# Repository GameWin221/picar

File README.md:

# picar
Car with autonomous and remote-controlled capabilities controlled by Raspberry Pi 5 and a CH32V003 microcontroller. Features a custom made mainboard PCB responsible for controlling motors, servos and delivering power to the RPi 5.

It is capable of real-time remote control with a gamepad (e.g. XBox One gamepad) alongside a live WebRTC stream from its camera.
Moreover, simple autonomous driving is possible by following an RGB tracking marker.

### Version 3 Early (still the old frame from V2)

*PiCar with the tracking marker next to it*

## Future ideas 
- Add a ToF sensor and use it in tandem with the DepthAnything V2 depth estimation model to acquire real (approximated) depth information from the camera.

# Hardware
- Battery pack composed of 3x 18650 cells connected in series. It has both XT60 connector for the main power and 4-pin JST-XH used for balancing.
- SG92R micro servo used for steering
- Raspberry Pi 5 8GB
- Raspberry Pi Camera HD v2 8MPx
- Custom PCB mainboard responsible for controlling motors, servos and delivering power to the RPi 5. (More on that [below](#pcb-mainboard))
- Custom 3D-printed frame and steering system (files available in the "designs" directory)
- 4x 60x8mm black Pololu 1420 wheels
- 2x 6x13x5mm bearings for the front wheels
- 2x N20-BT07 micro 100:1 320RPM 12V motors
- M3 screws used for assembling the frame and wheels together

## PCB mainboard

*/pcb_main_board/pcb_main_board_schematic.svg*

*/images/pcb_main_board1.png*

### On-board microcontroller

CH32V003 MCU is the main controller of the whole board. It is responsible for controlling the motor drivers, servo motors and monitoring the battery voltage. It communicates with the Raspberry Pi 5 over I2C.

### Battery to RPi 5 voltage step-down

The battery input voltage is first filtered by the input low-ESR capacitor and capped to 15V by a SMBJ15A TVS diode. Then the MP2338 IC is used to reliably step-down the battery voltage from 9V-12.6V range to ~5.1V that is then connected via a USB-C cable to the RPi 5. The MP2338's GND pin is connected to wide copper traces with vias in order to improve cooling.

### Motor control

TB6612FNG IC is used to drive both of the main motors. The IC logic is driven by PWM signals generated by the on-board microcontroller. The PWM frequency can be adjusted from the software layer if the user wants to prioritize peak power or to minimize the audible switching noise. The lower the frequency, the more efficient the motors are, but the louder they become.

### Servo control

The mainboard is capable of running 4 separate hardware PWM signals at once which are generated by the on-board microcontroller. The servo motors are powered with 4.8V generated by another MP2238 IC configured in the same way as the other one used for powering RPi 5, except for the output voltage. The servo section also has a 3-pin header for each signal channel in order to simplify the connections. There are more servo channels than are currently needed for future-proofing reasons. *e.g. allowing the camera to have adjustable yaw and pitch in the future.*

### Wheels

The front wheels are fastened to their mounts with short M3 screws. Those mounts then clip into the ball bearings, working similarly to LEGO Technic connections. A pin with the correct diameter and side cuts is pushed into the bearing hole and holds firmly enough for normal operation. The rear wheels are press-fitted onto the motor shafts:

Front wheel assembly disassembled in Fusion 360:

# Software and control

## Frontend
**PiCar** can be controlled through a simple Websockets-based web interface (`/car/software/index.html`). When you run the Python `"Remote Control" main loop` an HTTP server starts up and reveals the visual interface at `http://{raspberry_pi_5_ip}:8000`. There are two sliders that control it but the better (and way cooler) option is to **use a gamepad and control the car this way**. The website automatically detects connected gamepads and lets the user steer by using both triggers for accelerating and braking and the left thumbstick for steering. It is also possible to set the motors PWM switching frequency.

There also is a viewport for watching the live feed coming from the camera connected to the RPi 5. The stream source must be a WebRTC source which can be created easily by using [MediaMTX](https://github.com/bluenviron/mediamtx). You can find the working `mediamtx.yml` file I use to enable the stream at `/car/mediamtx.yml`. Once mediamtx starts with my provided config, the camera can be accessed by connecting via WebRTC to `{raspberry_pi_5_ip}:8889/rpi`.

## Vision

Autonomous driving, for now, is a simple computer vision algorithm that searches for a special marker with three key colors: red, green, and blue on the live feed streamed from the Raspberry Pi Camera HD v2 8MPx.

The camera feed is first filtered bilaterally to remove small details and noise in the subsequent marker search. Then gamma is adjusted to increase contrast, and the resulting image is binarized so that the SimpleBlobDetector from the OpenCV library can detect three circles. Finally, the algorithm checks whether the circles are "inside" the potentially found marker—i.e., whether they are not shifted from the averaged center by more than one standard deviation. If they are not, we can be certain that the marker has been found.

Below is a visualization of how the marker is seen by the algorithm:

When the marker is found, the vehicle drives forward and turns so that the center of the marker aligns with the center of the camera's view. This is sufficient to effectively track the marker.

### Future Vision Enhancement

I plan to use a ToF distance sensor in tandem with the computer vision model **DepthAnythingV2**, which estimates depth using a single camera. This combination will allow me to acquire approximate (yet sufficiently accurate) distance information of everything visible in the front camera. This data will enable shape detection by contours and autonomous obstacle avoidance.

## Firmware

The CH32V003 microcontroller runs a firmware that acts as a PWM and motor control interface for the Raspberry Pi 5. The firmware exposes a register-based interface over I2C using slave address `0x17`, allowing the RPi to elegantly control all aspects of motor and servo operation.

### I2C Communication Protocol

The firmware operates as an I2C slave that receives write-only commands structured as `[register_id, data_low, data_high]`. Each register controls a specific aspect of the system:

| Register | Purpose                           | Range            |
|----------|-----------------------------------|------------------|
| 1        | TIM1 (servo) frequency            | 1 - 48000 Hz     |
| 2        | TIM2 (motor) frequency            | 1 - 48000 Hz     |
| 4-7      | Servo CH1-CH4 duty cycle          | 0 - PWM_PERIOD(1000)         |
| 10-11    | Motor PWM (right/left) duty cycle | 0 - PWM_PERIOD(1000)         |
| 12       | Motor direction control           | Bit 0: DIRF, Bit 8: DIRB |

## Building the code

### RPi 5 Python
Configure the virtual environment if you need and run `pip install -r requirements.txt` while being in the `/car/software` directory to download the necessary packages. Downlaod opencv as a standalone package. Once everything is downloaded, run `python main.py` and it should work fine.

#### Enabling the necessary RPi 5 options
To make I2C communication work properly, enable it either with the `raspi-config` command or by manually adding the necessary lines to the `/boot/firmware/config.txt` file:

```
dtparam=i2c_arm=on
dtparam=i2c_arm_baudrate=80000 # or any other as you wish
dtparam=i2s=on
```

Also enable the camera detection in the same way. Here is the line for `/boot/firmware/config.txt`:

```
camera_auto_detect=1
```

### CH32V003 C Firmware
Downloading and building it through MounRiver Studio IDE is the easiest route to go. This repo already has project files that work out of the box when you open them with the IDE. Just press F7 and it should build perfectly fine.

#### Flashing it
You'll need a **WCH LinkE** programmer in order to flash the firmware to the chip. Once you have it, connect GND to GND and the SWDIO pin to the chip's SWIO pin according to its datasheet *(It's pin PD1 for CH32V003A4M6)*. The chip must be powered either from the programmer's voltage pin or externally during flashing.

Now go to MounRiver Studio IDE and press F7 to build your project and then F8 to flash it having the WCH LinkE programmer plugged into your computer at the same time, **note that flashing your code does not rebuild it automatically, you have to remember to press F7 each time.**. You can also change the flashing configuration but it's almost always good to go by default. *(called Download Configuration)*:

Do not press or hold the reset button during flashing (the NRST pin)

# Archive

Take a look at the [PROGRESS.md markdown file](/PROGRESS.md) to see how the project evolved over time.

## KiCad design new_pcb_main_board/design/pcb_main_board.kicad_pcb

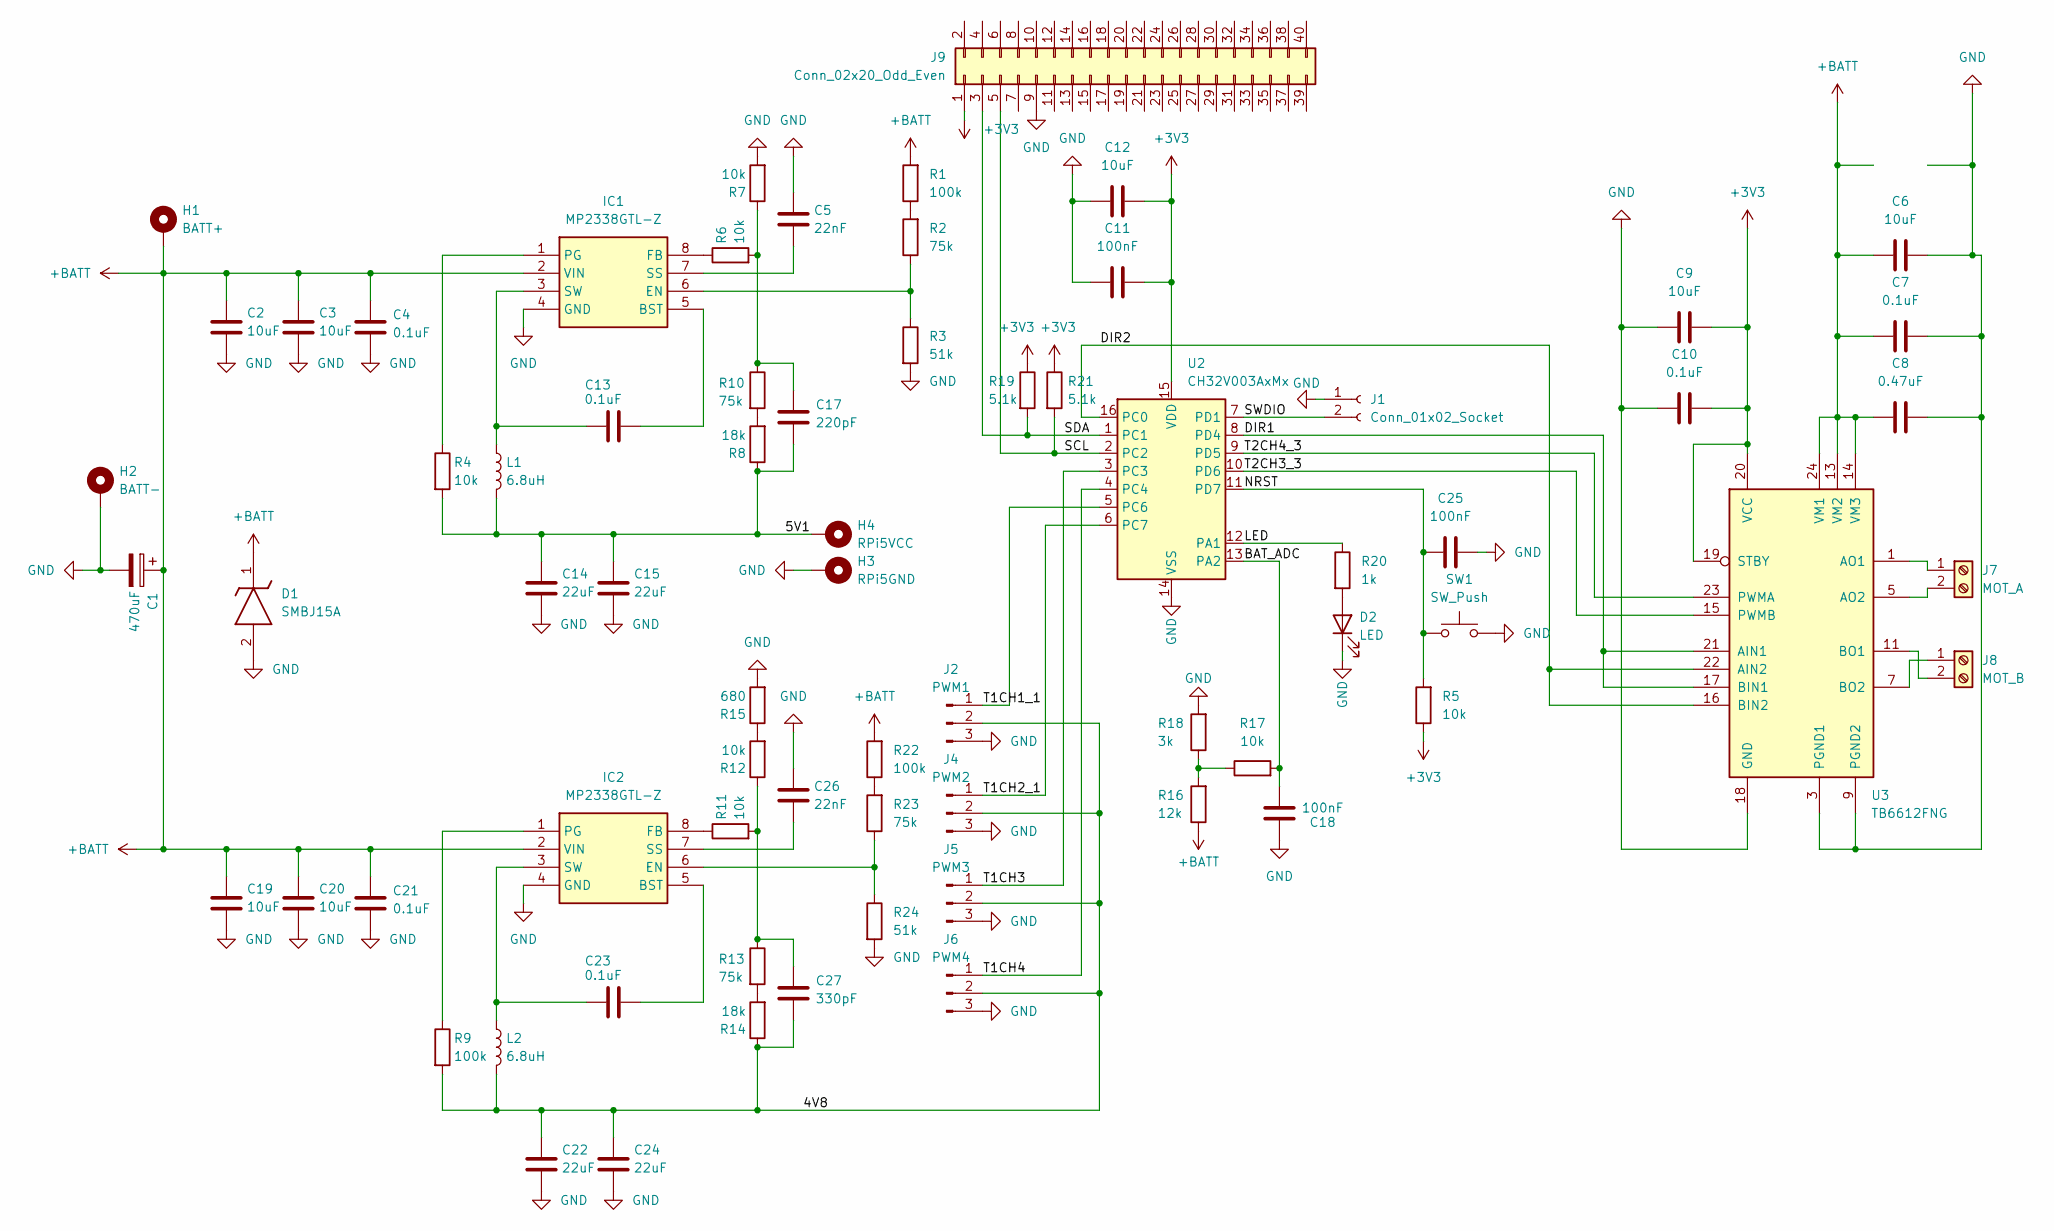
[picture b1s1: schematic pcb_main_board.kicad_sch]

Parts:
C1: 470uF; CP_Radial_D8.0mm_P3.50mm
C2, C3, C6, C9, C12, C19, C20: 10uF; C_0805_2012Metric
C4, C7, C10, C13, C21, C23: 0.1uF; C_0805_2012Metric
C5, C26: 22nF; C_0805_2012Metric
C8: 0.47uF; C_0805_2012Metric
C11, C18, C25: 100nF; C_0805_2012Metric
C14, C15, C22, C24: 22uF; C_0805_2012Metric_Pad1.18x1.45mm_HandSolder
C17: 220pF; C_0805_2012Metric
C27: 330pF; C_0805_2012Metric
D1: SMBJ15A; DIOM5436X244N; Mouser Part Number 78-SMBJ15A
D2: LED; LED_0805_2012Metric_Pad1.15x1.40mm_HandSolder
H1: BATT+; SolderWire-1sqmm_1x01_D1.4mm_OD3.9mm
H2: BATT-; SolderWire-1sqmm_1x01_D1.4mm_OD3.9mm
H3: RPi5GND; SolderWire-0.5sqmm_1x01_D0.9mm_OD2.3mm
H4: RPi5VCC; SolderWire-0.5sqmm_1x01_D0.9mm_OD2.3mm
IC1, IC2: MP2338GTL-Z; SOT-583-8; Mouser Part Number 946-MP2338GTL-Z
J1: Conn_01x02_Socket; PinSocket_1x02_P2.54mm_Vertical
J2: PWM1; PinHeader_1x03_P2.54mm_Vertical
J4: PWM2; PinHeader_1x03_P2.54mm_Vertical
J5: PWM3; PinHeader_1x03_P2.54mm_Vertical
J6: PWM4; PinHeader_1x03_P2.54mm_Vertical
J7: MOT_A; TerminalBlock_MaiXu_MX126-5.0-02P_1x02_P5.00mm
J8: MOT_B; TerminalBlock_MaiXu_MX126-5.0-02P_1x02_P5.00mm
J9: Conn_02x20_Odd_Even; PinSocket_2x20_P2.54mm_Vertical
L1, L2: 6.8uH; L_Chilisin_BMRF00101040
R1, R9, R22: 100k; R_0805_2012Metric
R2, R10, R13, R23: 75k; R_0805_2012Metric
R3, R24: 51k; R_0805_2012Metric
R4, R5, R6, R7, R11, R12, R17: 10k; R_0805_2012Metric
R8, R14: 18k; R_0805_2012Metric
R15: 680; R_0805_2012Metric
R16: 12k; R_0805_2012Metric
R18: 3k; R_0805_2012Metric
R19, R21: 5.1k; R_0805_2012Metric
R20: 1k; R_0805_2012Metric
SW1: SW_Push; SW_PUSH_6mm
U2: CH32V003AxMx; STC_SOP-16_3.9x9.9mm_P1.27mm
U3: TB6612FNG; SSOP-24_5.3x8.2mm_P0.65mm

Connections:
+3V3: C9.2, C10.2, C11.2, C12.2, J9.1, R5.1, R19.1, R21.1, U2.15 (VDD), U3.19 (STBY), U3.20 (VCC)
+BATT: C1.1, C2.1, C3.1, C4.1, C6.1, C7.1, C8.1, C19.1, C20.1, C21.1, D1.1 (K), H1.1, IC1.2 (VIN), IC2.2 (VIN), R1.2, R16.1, R22.2, U3.13 (VM2), U3.14 (VM3), U3.24 (VM1)
/4V8: C22.1, C24.1, C27.2, J2.2, J4.2, J5.2, J6.2, L2.2, R9.2, R14.1
/5V1: C14.1, C15.1, C17.2, H4.1, L1.2, R4.2, R8.1
/BAT_ADC: C18.2, R17.2, U2.13 (PA2)
/DIR1: U2.8 (PD4), U3.17 (BIN1), U3.21 (AIN1)
/DIR2: U2.16 (PC0), U3.16 (BIN2), U3.22 (AIN2)
/LED: R20.1, U2.12 (PA1)
/NRST: C25.1, R5.2, SW1.1, U2.11 (PD7)
/SCL: J9.5, R21.2, U2.2 (PC2)
/SDA: J9.3, R19.2, U2.1 (PC1)
/SWDIO: J1.2, U2.7 (PD1)
/T1CH1_1: J2.1, U2.5 (PC6)
/T1CH2_1: J4.1, U2.6 (PC7)
/T1CH3: J5.1, U2.3 (PC3)
/T1CH4: J6.1, U2.4 (PC4)
/T2CH3_3: U2.10 (PD6), U3.15 (PWMB)
/T2CH4_3: U2.9 (PD5), U3.23 (PWMA)
GND: C1.2, C2.2, C3.2, C4.2, C5.1, C6.2, C7.2, C8.2, C9.1, C10.1, C11.1, C12.1, C14.2, C15.2, C18.1, C19.2, C20.2, C21.2, C22.2, C24.2, C25.2, C26.1, D1.2 (A), D2.1 (K), H2.1, H3.1, IC1.4 (GND), IC2.4 (GND), J1.1, J2.3, J4.3, J5.3, J6.3, J9.9, R3.2, R7.2, R15.2, R18.2, R24.2, SW1.2, U2.14 (VSS), U3.3 (PGND1), U3.4 (PGND1), U3.9 (PGND2), U3.10 (PGND2), U3.18 (GND)
unnamed: C17.1, R6.2, R7.1, R10.1
unnamed: C27.1, R11.2, R12.1, R13.1
unnamed: D2.2 (A), R20.2
unnamed: C13.2, IC1.5 (BST)
unnamed: IC1.6 (EN), R2.1, R3.1
unnamed: IC1.8 (FB), R6.1
unnamed: IC1.1 (PG), R4.1
unnamed: C5.2, IC1.7 (SS)
unnamed: C13.1, IC1.3 (SW), L1.1
unnamed: C23.2, IC2.5 (BST)
unnamed: IC2.6 (EN), R23.1, R24.1
unnamed: IC2.8 (FB), R11.1
unnamed: IC2.1 (PG), R9.1
unnamed: C26.2, IC2.7 (SS)
unnamed: C23.1, IC2.3 (SW), L2.1
unnamed: J7.1, U3.1 (AO1), U3.2 (AO1)
unnamed: J7.2, U3.5 (AO2), U3.6 (AO2)
unnamed: J8.1, U3.7 (BO2), U3.8 (BO2)
unnamed: J8.2, U3.11 (BO1), U3.12 (BO1)
unnamed: R1.1, R2.2
unnamed: R8.2, R10.2
unnamed: R12.2, R15.1
unnamed: R13.2, R14.2
unnamed: R16.2, R17.1, R18.1
unnamed: R22.1, R23.2

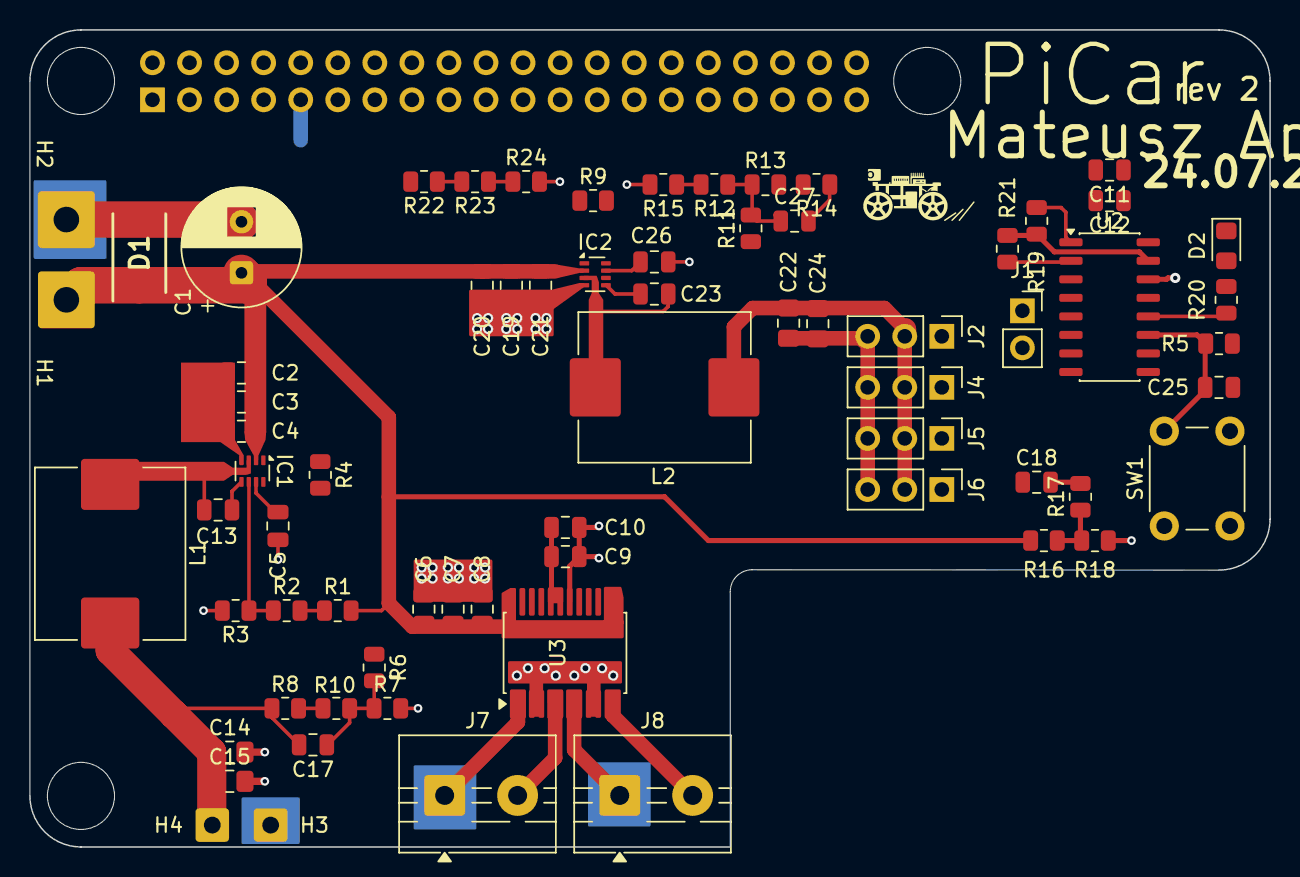
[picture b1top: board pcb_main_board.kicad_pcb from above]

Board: 2 copper layers, 85.0 x 56.0 mm, 71 parts (1 on the bottom side), 44 nets.

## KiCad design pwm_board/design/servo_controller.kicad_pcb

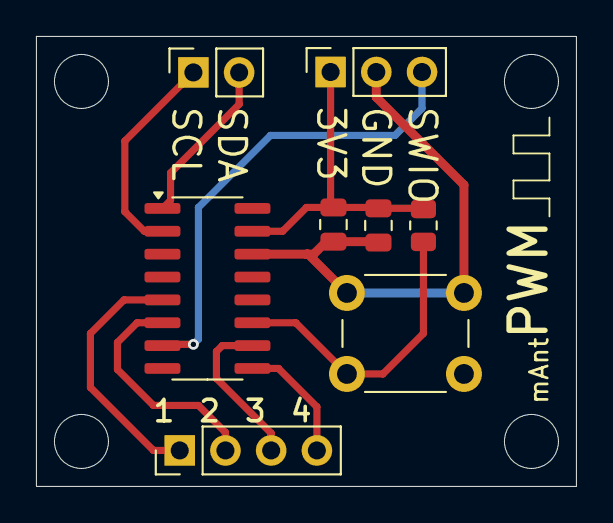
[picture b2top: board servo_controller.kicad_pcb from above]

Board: 2 copper layers, 30.0 x 25.0 mm, 8 parts (0 on the bottom side), 10 nets.

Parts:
C1: 10u; C_0805_2012Metric
C2: 100n; C_0805_2012Metric
J1: Conn_01x03_Socket; PinSocket_1x03_P2.54mm_Vertical
J3: Conn_01x02_Socket; PinSocket_1x02_P2.54mm_Vertical
J5: Conn_01x04_Pin; PinHeader_1x04_P2.54mm_Vertical
R1: 10k; R_0805_2012Metric
SW1: SW_Push; SW_PUSH_6mm
U1: CH32V003AxMx; SOP-16_3.9x9.9mm_P1.27mm

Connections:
+3V3: C1.1, C2.1, J1.1, R1.2, U1.15 (VDD)
/SCL: J3.1, U1.2 (PC2)
/SDA: J3.2, U1.1 (PC1)
/SWDIO: J1.3, U1.7 (PD1)
/T1CH1_1: J5.1, U1.5 (PC6)
/T1CH2_1: J5.2, U1.6 (PC7)
/T2CH3_3: J5.3, U1.10 (PD6)
/T2CH4_3: J5.4, U1.9 (PD5)
GND: C1.2, C2.2, J1.2, SW1.2, U1.14 (VSS)
unnamed: R1.1, SW1.1, U1.11 (PD7)

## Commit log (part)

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2025-05-27 readme
2025-08-15 New frame and mAntPWM CH32V003 board
2025-08-15 Better README
2025-08-17 Update readabilty
2025-11-05 PCB Main Board Design
2025-11-07 List of Mouser footprints
2026-01-24 V3 Early Upload
    The software doesn't work yet
2026-01-24 Fix schematic in the README
2026-04-12 V3 firmware, software and better README
2026-04-12 Fix pcb schematic svg
2026-04-12 Update README to include CH32V003 microcontroller
2026-06-27 Began working on the final PCB revision
